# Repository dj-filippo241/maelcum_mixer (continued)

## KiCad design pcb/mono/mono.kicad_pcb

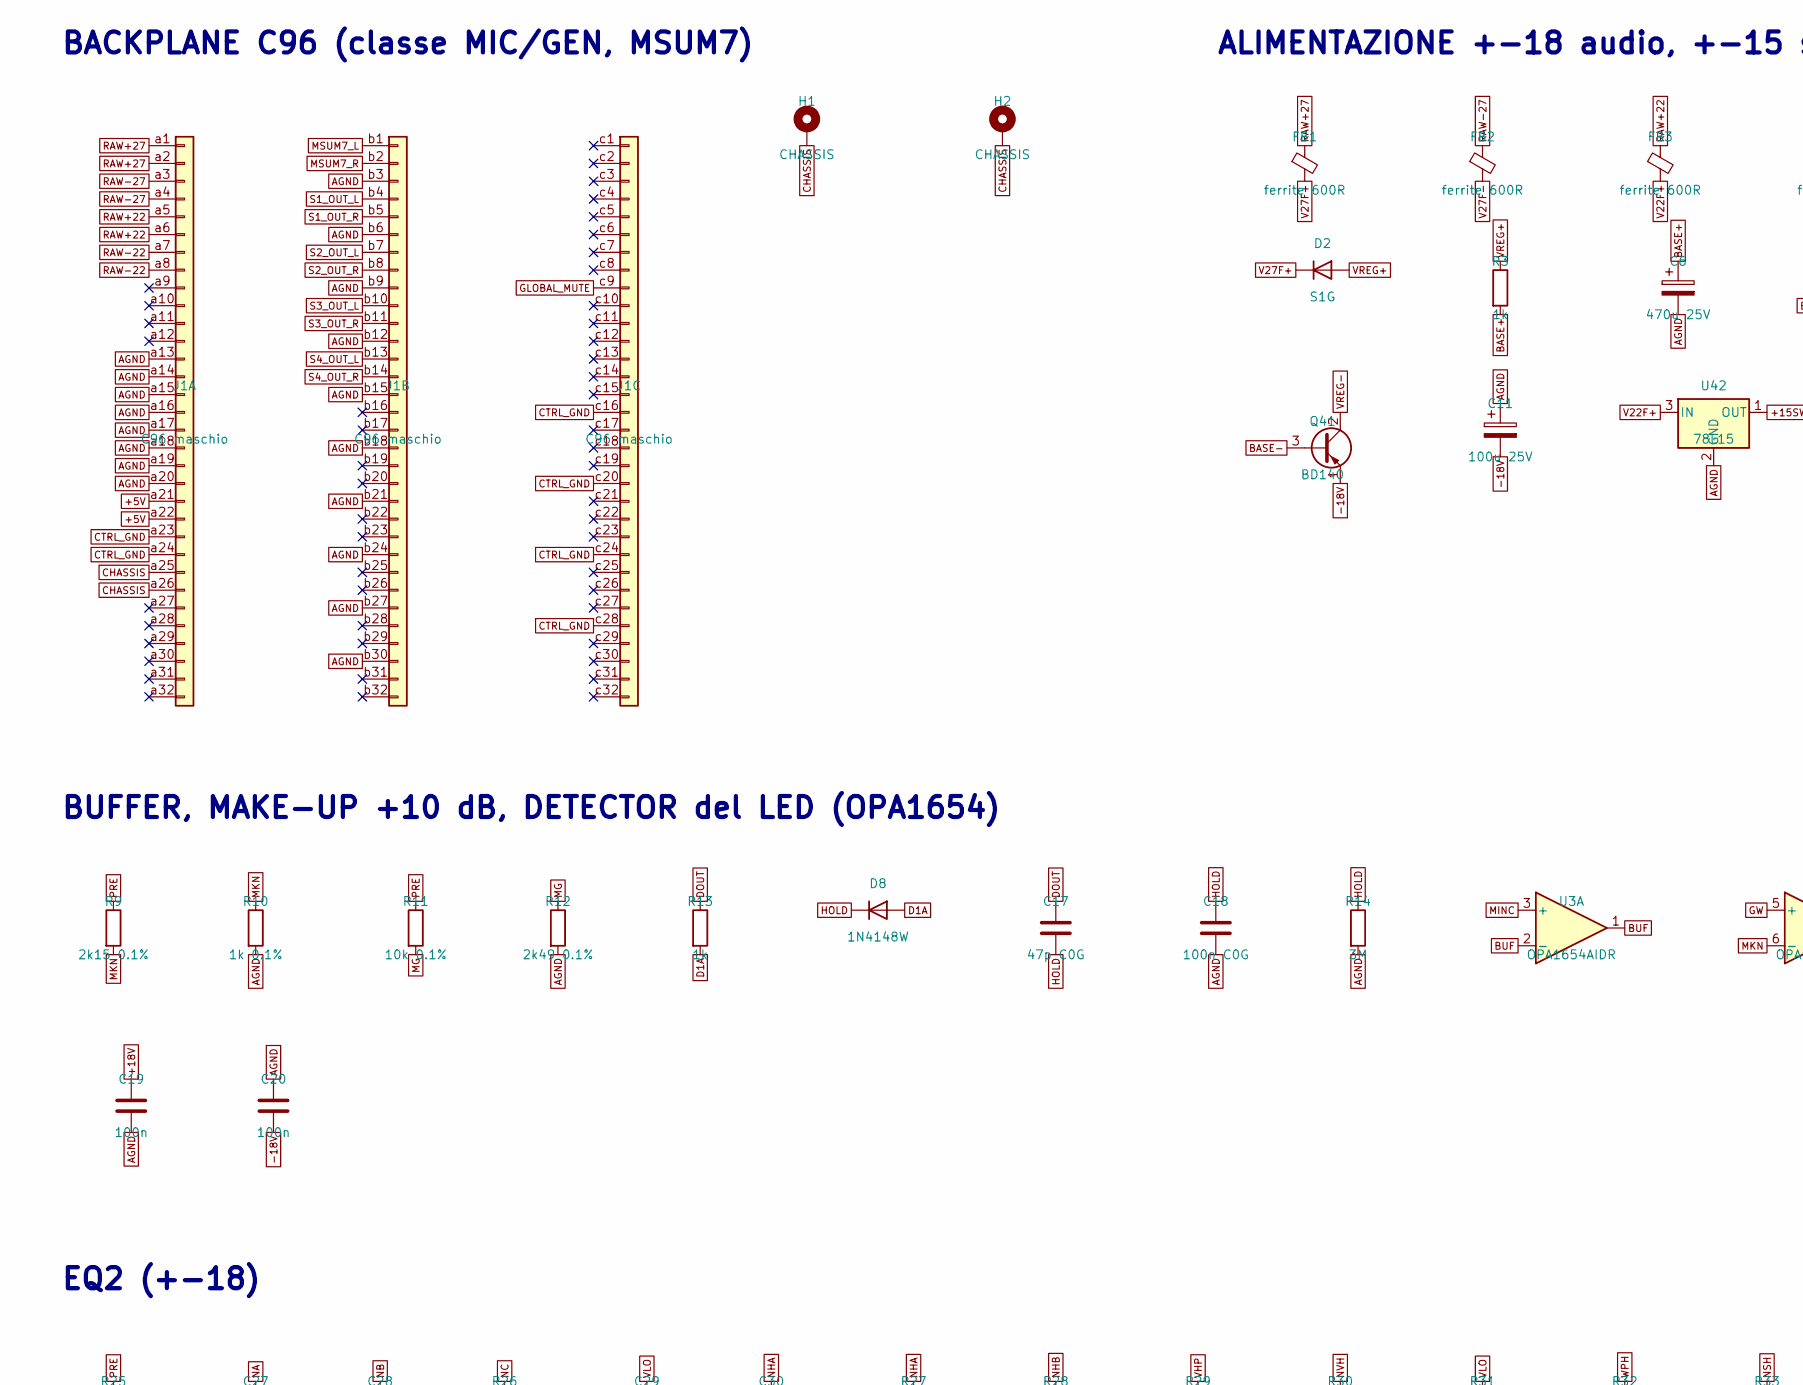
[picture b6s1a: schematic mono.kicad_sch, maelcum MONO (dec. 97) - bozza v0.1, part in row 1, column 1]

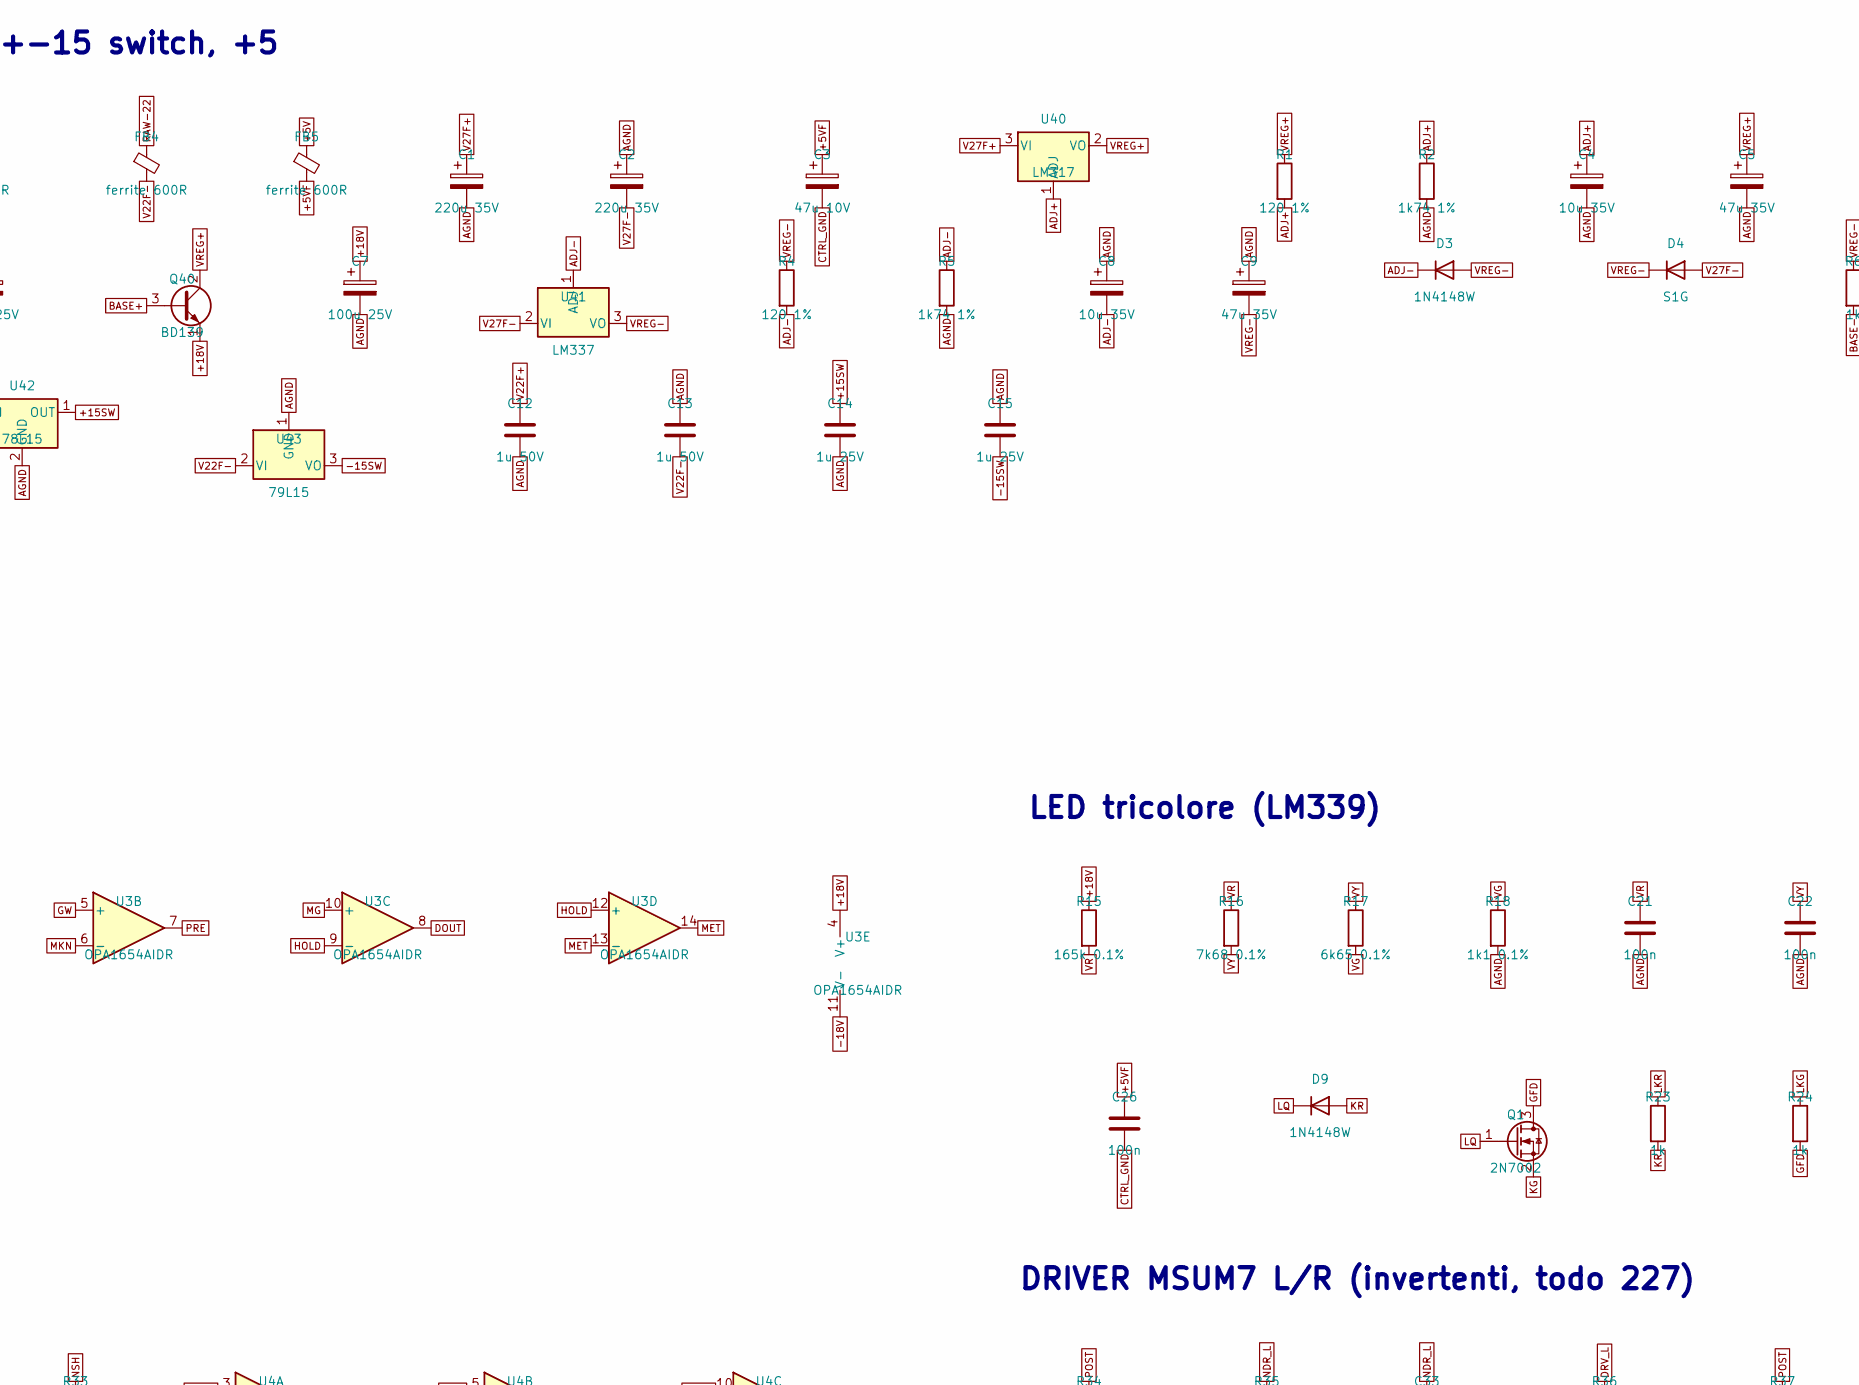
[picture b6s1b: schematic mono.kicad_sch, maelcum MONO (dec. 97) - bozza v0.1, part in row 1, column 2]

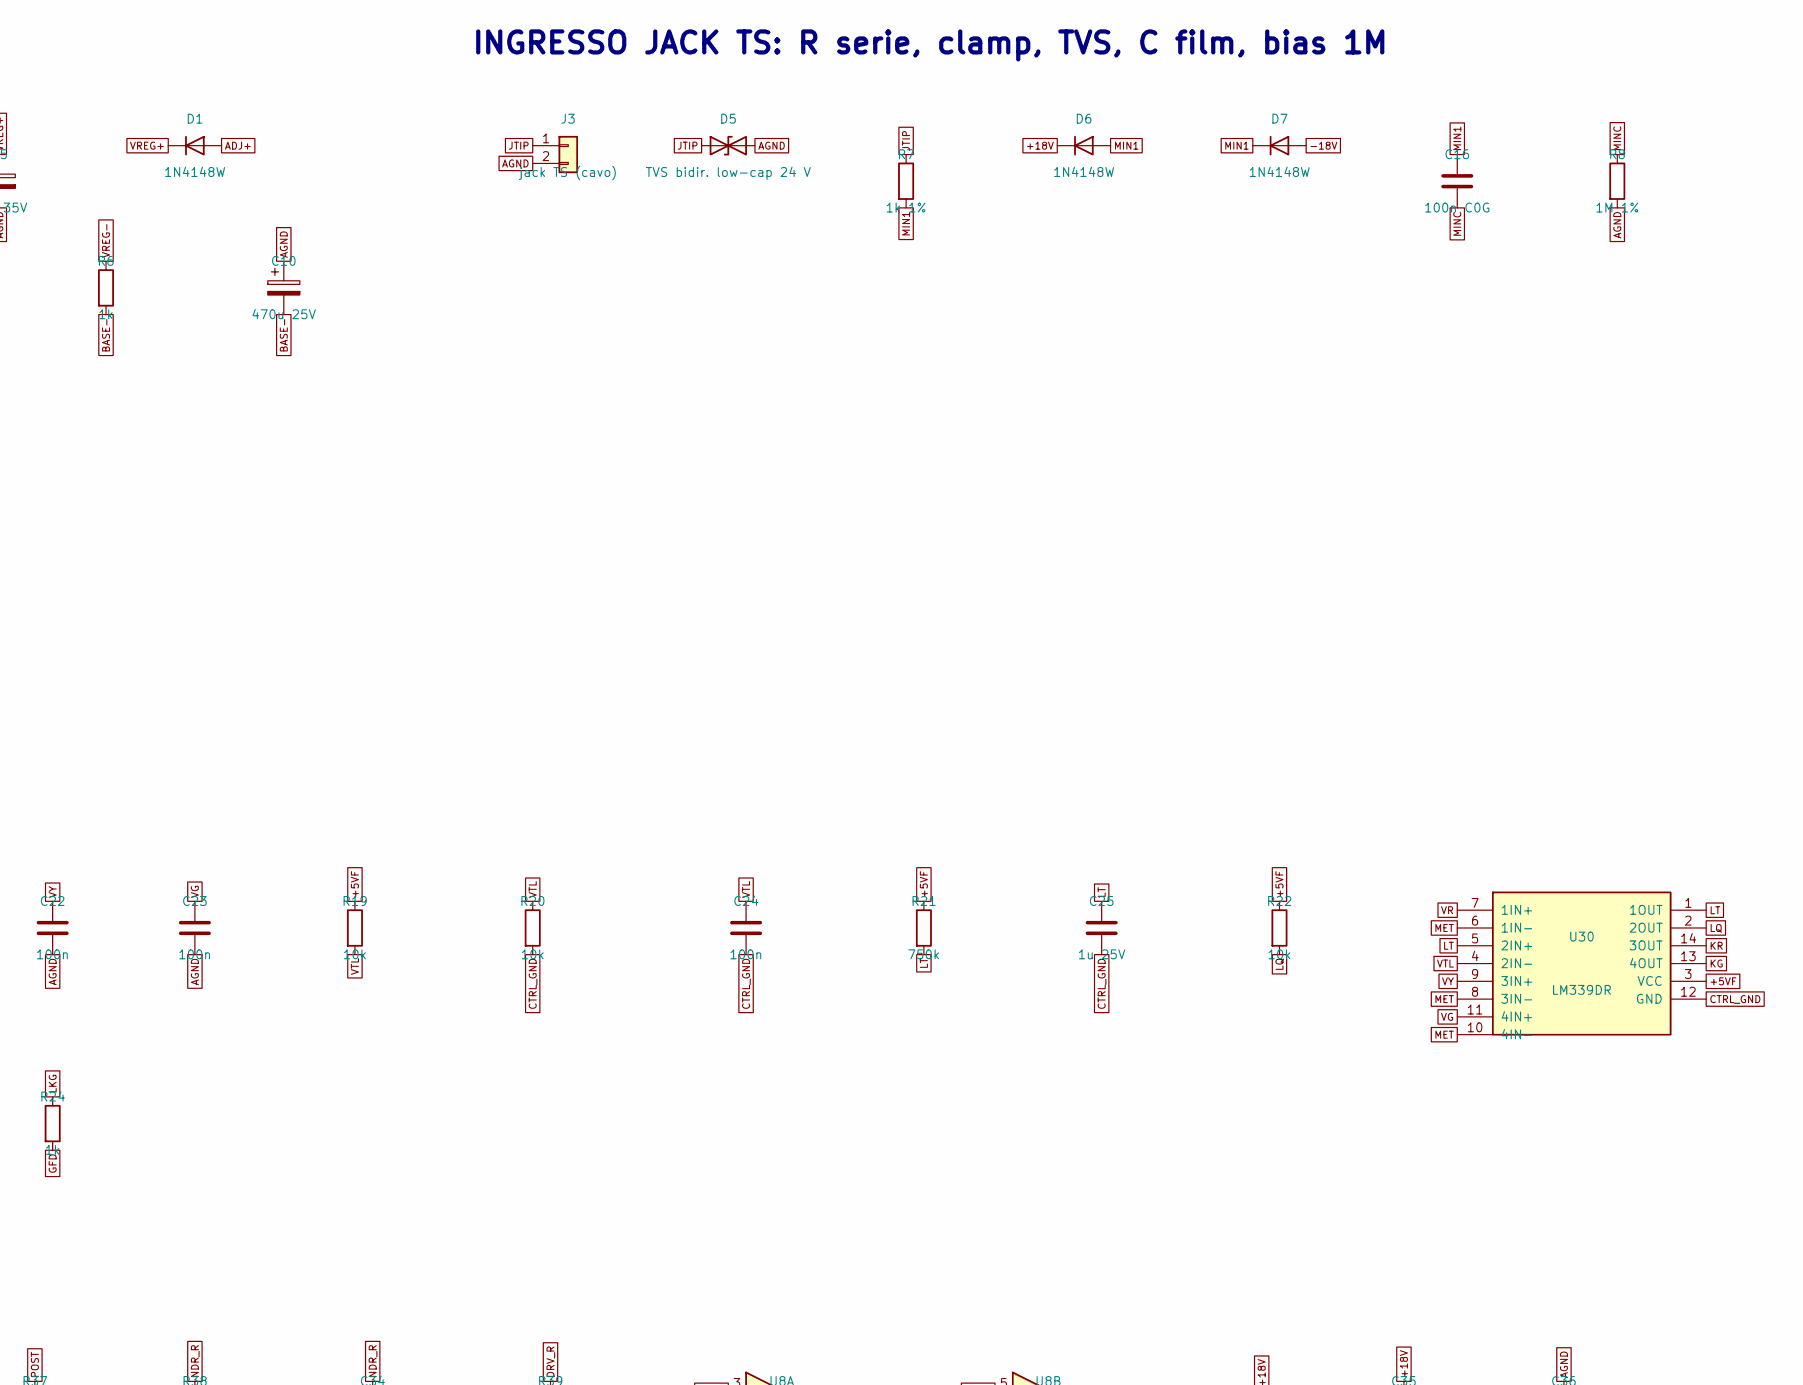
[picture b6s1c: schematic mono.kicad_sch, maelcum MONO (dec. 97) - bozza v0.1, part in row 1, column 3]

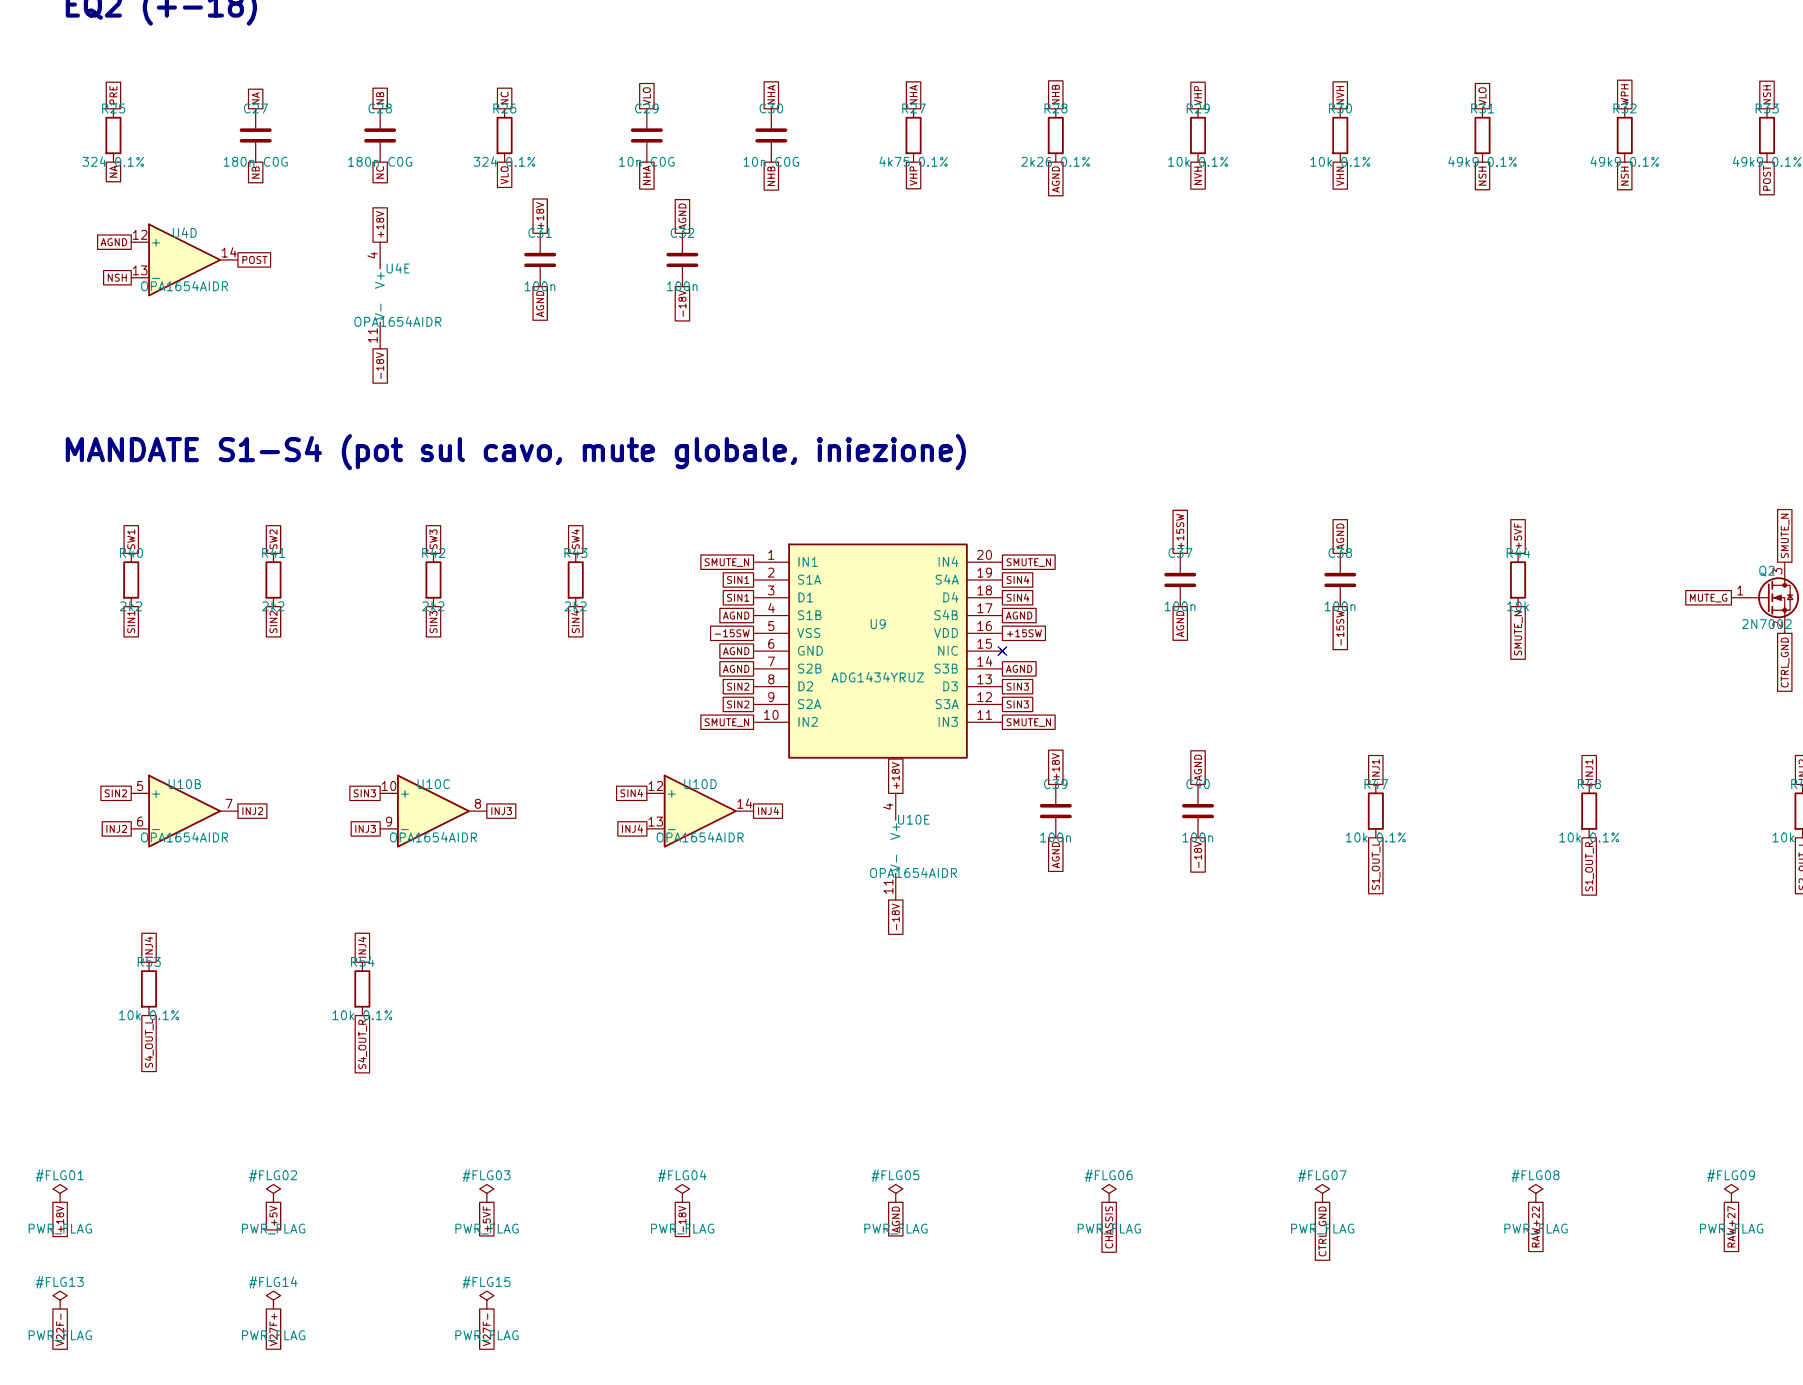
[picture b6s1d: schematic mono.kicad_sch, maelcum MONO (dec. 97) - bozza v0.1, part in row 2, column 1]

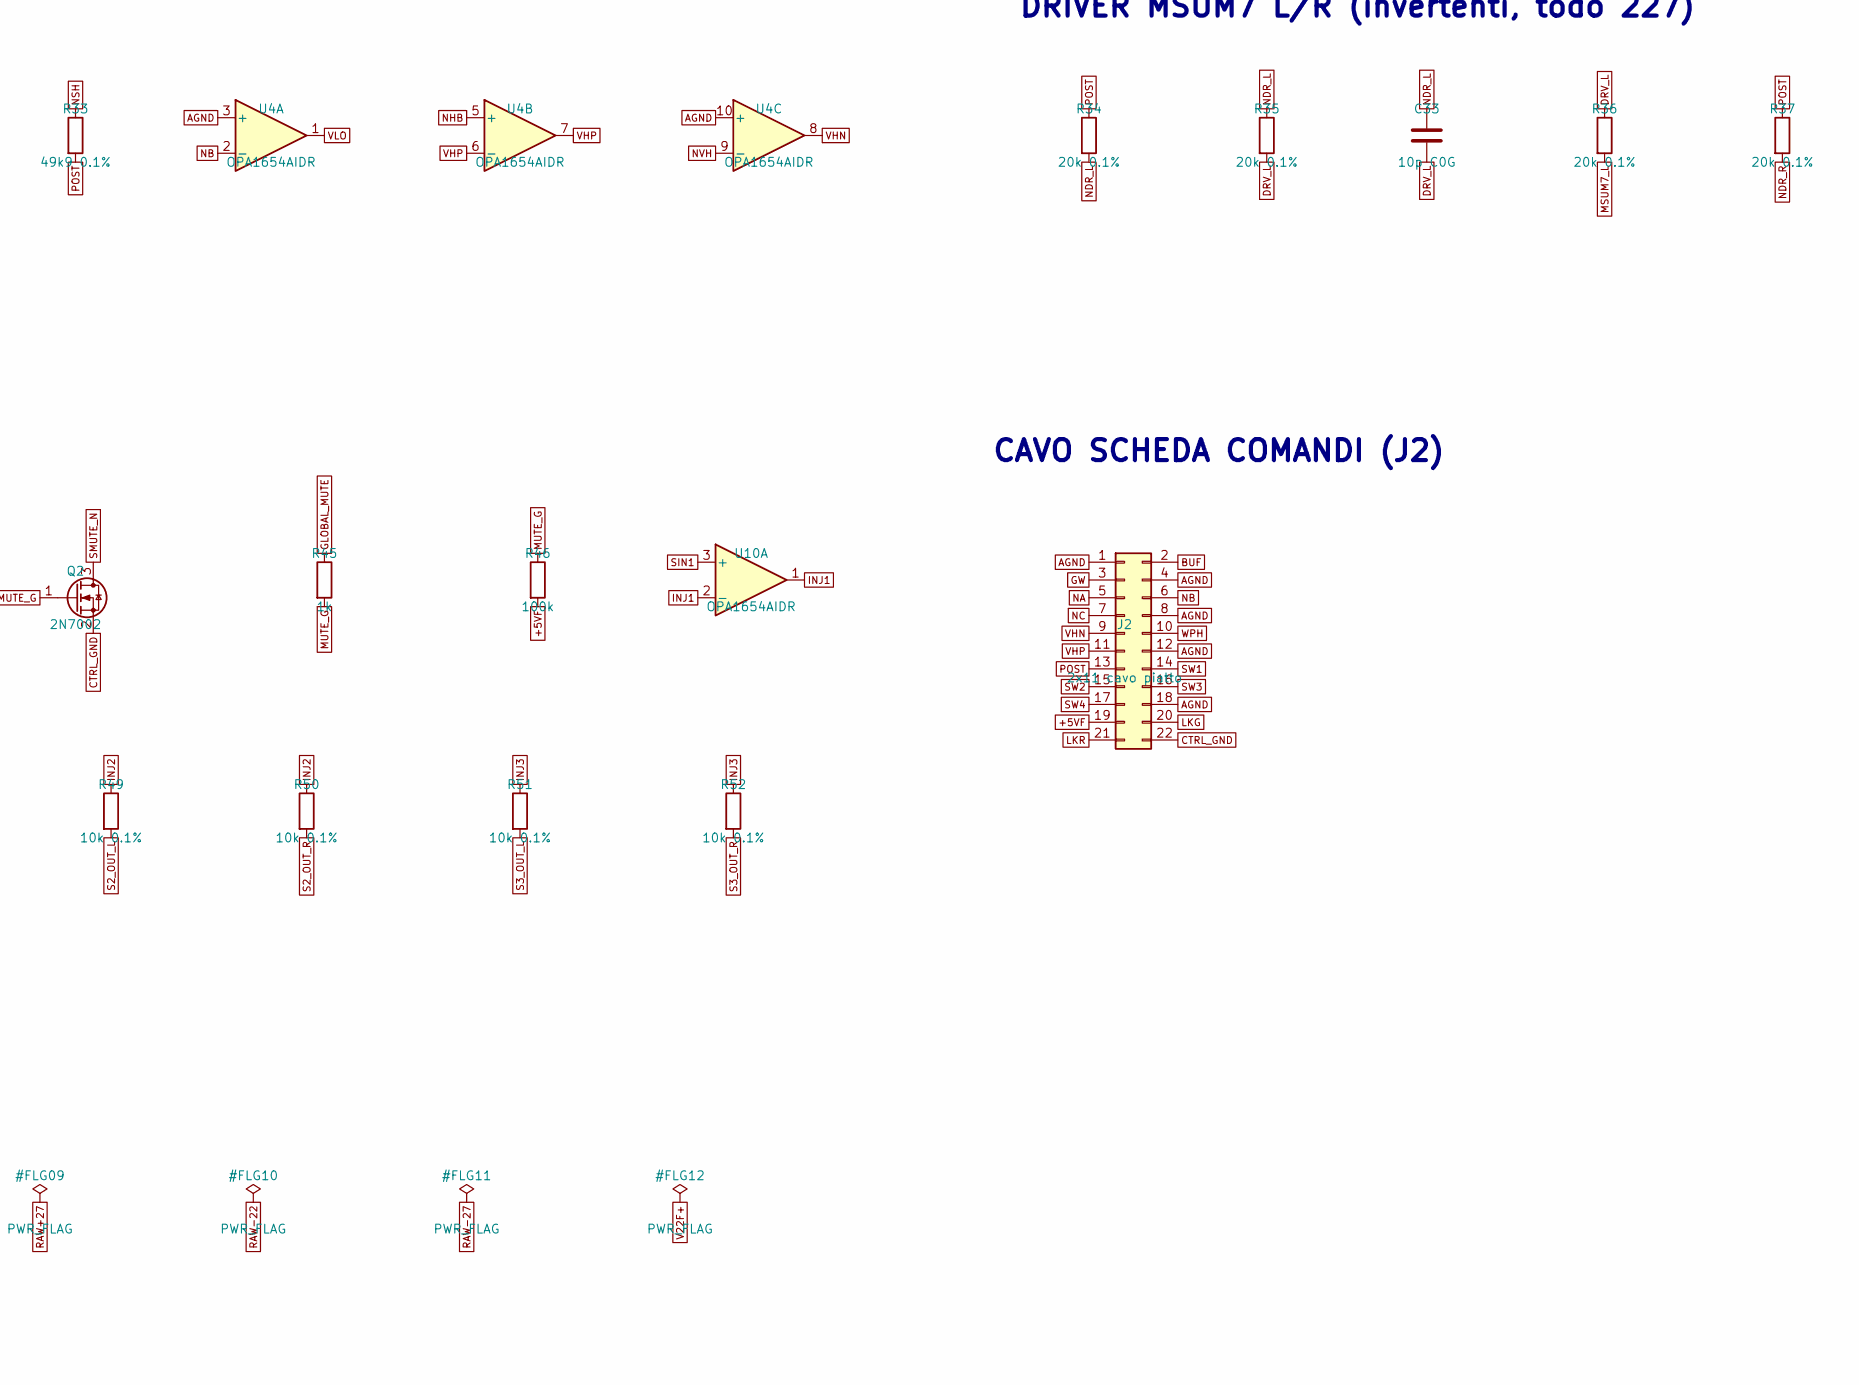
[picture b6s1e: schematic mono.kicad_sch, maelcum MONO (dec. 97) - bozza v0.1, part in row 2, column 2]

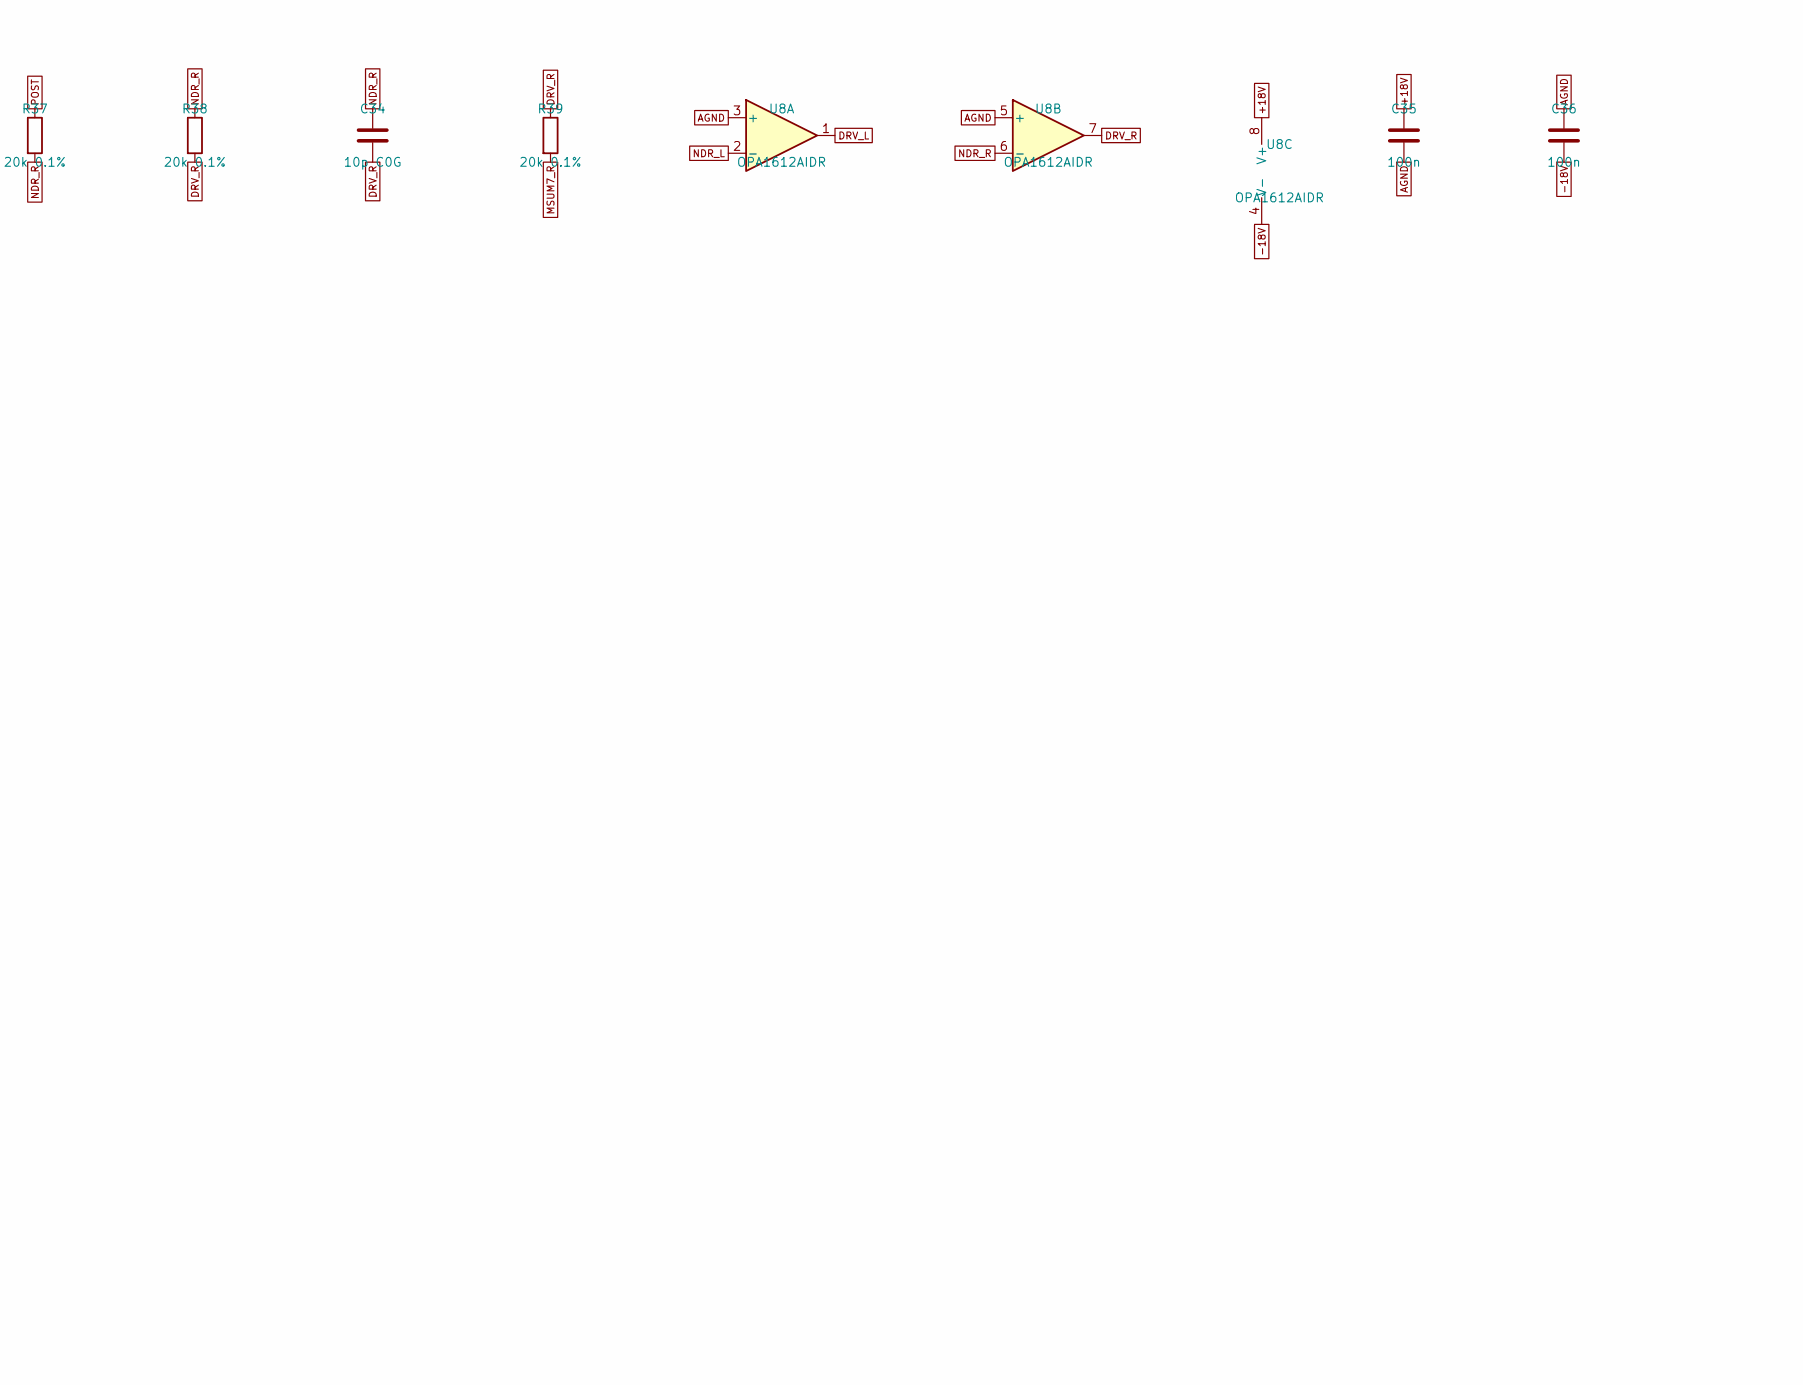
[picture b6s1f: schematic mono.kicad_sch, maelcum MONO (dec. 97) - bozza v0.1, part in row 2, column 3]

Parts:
C1, C2: 220u 35V; CP_Radial_D8.0mm_P3.50mm
C3: 47u 10V; CP_Radial_D5.0mm_P2.00mm
C4, C8: 10u 35V; CP_Radial_D5.0mm_P2.00mm
C5, C9: 47u 35V; CP_Radial_D6.3mm_P2.50mm
C6, C10: 470u 25V; CP_Radial_D8.0mm_P3.50mm
C7, C11: 100u 25V; CP_Radial_D6.3mm_P2.50mm
C12, C13: 1u 50V; C_1206_3216Metric
C14, C15, C25: 1u 25V; C_1206_3216Metric
C16, C18: 100n C0G; C_1206_3216Metric
C17: 47p C0G; C_0805_2012Metric
C19, C20, C21, C22, C23, C24, C26, C31, C32, C35, C36, C37, C38, C39, C40: 100n; C_0805_2012Metric
C27, C28: 180n C0G; C_1206_3216Metric
C29, C30: 10n C0G; C_1206_3216Metric
C33, C34: 10p C0G; C_0805_2012Metric
D1, D3, D6, D7, D8, D9: 1N4148W; D_SOD-123
D2, D4: S1G; D_SMA
D5: TVS bidir. low-cap 24 V; D_SOD-323
FB1, FB2, FB3, FB4, FB5: ferrite 600R; L_1206_3216Metric
H1, H2: CHASSIS; MountingHole_3.2mm_M3_Pad
J1: C96 maschio; DIN41612_C_3x32_Male_Horizontal_THT
J2: 2x11 cavo piatto; PinHeader_2x11_P2.54mm_Vertical
J3: jack TS (cavo); PinHeader_1x02_P2.54mm_Vertical
Q1, Q2: 2N7002; SOT-23
Q40: BD139; TO-126-3_Vertical
Q41: BD140; TO-126-3_Vertical
R1, R4: 120 1%; R_0805_2012Metric
R2, R5: 1k74 1%; R_0805_2012Metric
R3, R6, R13, R23, R24, R45: 1k; R_0805_2012Metric
R7: 1k 1%; R_0805_2012Metric
R8: 1M 1%; R_0805_2012Metric
R9: 2k15 0.1%; R_0805_2012Metric
R10: 1k 0.1%; R_0805_2012Metric
R11, R29, R30, R47, R48, R49, R50, R51, R52, R53, R54: 10k 0.1%; R_0805_2012Metric
R12: 2k49 0.1%; R_0805_2012Metric
R14: 3M; R_0805_2012Metric
R15: 165k 0.1%; R_0805_2012Metric
R16: 7k68 0.1%; R_0805_2012Metric
R17: 6k65 0.1%; R_0805_2012Metric
R18: 1k1 0.1%; R_0805_2012Metric
R19, R20, R22, R44: 10k; R_0805_2012Metric
R21: 750k; R_0805_2012Metric
R25, R26: 324 0.1%; R_0805_2012Metric
R27: 4k75 0.1%; R_0805_2012Metric
R28: 2k26 0.1%; R_0805_2012Metric
R31, R32, R33: 49k9 0.1%; R_0805_2012Metric
R34, R35, R36, R37, R38, R39: 20k 0.1%; R_0805_2012Metric
R40, R41, R42, R43: 2k2; R_0805_2012Metric
R46: 100k; R_0805_2012Metric
U3, U4, U10: OPA1654AIDR; SOIC-14_3.9x8.7mm_P1.27mm
U8: OPA1612AIDR; SOIC-8_3.9x4.9mm_P1.27mm
U9: ADG1434YRUZ; TSSOP-20_4.4x6.5mm_P0.65mm
U30: LM339DR; SOIC-14_3.9x8.7mm_P1.27mm
U40: LM317; TO-220-3_Vertical
U41: LM337; TO-220-3_Vertical
U42: 78L15; SOT-89-3
U43: 79L15; SOT-89-3

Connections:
+5V: FB5.1, J1.a21, J1.a22
+5VF: C3.1, C26.1, FB5.2, J2.19, R19.1, R21.1, R22.1, R44.1, R46.2, U30.3 (VCC)
+15SW: C14.1, C37.1, U9.16 (VDD), U42.1 (OUT)
+18V: C7.1, C19.1, C31.1, C35.1, C39.1, D6.1 (K), Q40.1 (E), R15.1, U3.4 (V+), U4.4 (V+), U8.8 (V+), U10.4 (V+)
-15SW: C15.2, C38.2, U9.5 (VSS), U43.3 (VO)
-18V: C11.2, C20.2, C32.2, C36.2, C40.2, D7.2 (A), Q41.1 (E), U3.11 (V-), U4.11 (V-), U8.4 (V-), U10.11 (V-)
ADJ+: C4.1, D1.2 (A), R1.2, R2.1, U40.1 (ADJ)
ADJ-: C8.2, D3.1 (K), R4.2, R5.1, U41.1 (ADJ)
AGND: C1.2, C2.1, C4.2, C5.2, C6.2, C7.2, C8.1, C9.1, C10.1, C11.1, C12.2, C13.1, C14.2, C15.1, C18.2, C19.2, C20.1, C21.2, C22.2, C23.2, C31.2, C32.1, C35.2, C36.1, C37.2, C38.1, C39.2, C40.1, D5.2 (A2), J1.a13, J1.a14, J1.a15, J1.a16, J1.a17, J1.a18, J1.a19, J1.a20, J1.b3, J1.b6, J1.b9, J1.b12, J1.b15, J1.b18, J1.b21, J1.b24, J1.b27, J1.b30, J2.1, J2.4, J2.8, J2.12, J2.18, J3.2, R2.2, R5.2, R8.2, R10.2, R12.2, R14.2, R18.2, R28.2, U4.3 (+), U4.10 (+), U4.12 (+), U8.3 (+), U8.5 (+), U9.4 (S1B), U9.6 (GND), U9.7 (S2B), U9.14 (S3B), U9.17 (S4B), U42.2 (GND), U43.1 (GND)
BASE+: C6.1, Q40.3 (B), R3.2
BASE-: C10.2, Q41.3 (B), R6.2
BUF: J2.2, U3.1, U3.2 (-)
CHASSIS: H1.1, H2.1, J1.a25, J1.a26
CTRL_GND: C3.2, C24.2, C25.2, C26.2, J1.a23, J1.a24, J1.c16, J1.c20, J1.c24, J1.c28, J2.22, Q2.2 (S), R20.2, U30.12 (GND)
D1A: D8.2 (A), R13.2
DOUT: C17.1, R13.1, U3.8
DRV_L: C33.2, R35.2, R36.1, U8.1
DRV_R: C34.2, R38.2, R39.1, U8.7
GFD: Q1.3 (D), R24.2
GLOBAL_MUTE: J1.c9, R45.1
GW: J2.3, U3.5 (+)
HOLD: C17.2, C18.1, D8.1 (K), R14.1, U3.9 (-), U3.12 (+)
INJ1: R47.1, R48.1, U10.1, U10.2 (-)
INJ2: R49.1, R50.1, U10.6 (-), U10.7
INJ3: R51.1, R52.1, U10.8, U10.9 (-)
INJ4: R53.1, R54.1, U10.13 (-), U10.14
JTIP: D5.1 (A1), J3.1, R7.1
KG: Q1.2 (S), U30.13 (4OUT)
KR: D9.2 (A), R23.2, U30.14 (3OUT)
LKG: J2.20, R24.1
LKR: J2.21, R23.1
LQ: D9.1 (K), Q1.1 (G), R22.2, U30.2 (2OUT)
LT: C25.1, R21.2, U30.1 (1OUT), U30.5 (2IN+)
MET: U3.13 (-), U3.14, U30.6 (1IN-), U30.8 (3IN-), U30.10 (4IN-)
MG: R11.2, R12.1, U3.10 (+)
MIN1: C16.1, D6.2 (A), D7.1 (K), R7.2
MINC: C16.2, R8.1, U3.3 (+)
MKN: R9.2, R10.1, U3.6 (-)
MSUM7_L: J1.b1, R36.2
MSUM7_R: J1.b2, R39.2
MUTE_G: Q2.1 (G), R45.2, R46.1
NA: C27.1, J2.5, R25.2
NB: C27.2, C28.1, J2.6, U4.2 (-)
NC: C28.2, J2.7, R26.1
NDR_L: C33.1, R34.2, R35.1, U8.2 (-)
NDR_R: C34.1, R37.2, R38.1, U8.6 (-)
NHA: C29.2, C30.1, R27.1
NHB: C30.2, R28.1, U4.5 (+)
NSH: R31.2, R32.2, R33.1, U4.13 (-)
NVH: R29.2, R30.1, U4.9 (-)
POST: J2.13, R33.2, R34.1, R37.1, U4.14
PRE: R9.1, R11.1, R25.1, U3.7
RAW+22: FB3.1, J1.a5, J1.a6
RAW+27: FB1.1, J1.a1, J1.a2
RAW-22: FB4.1, J1.a7, J1.a8
RAW-27: FB2.1, J1.a3, J1.a4
S1_OUT_L: J1.b4, R47.2
S1_OUT_R: J1.b5, R48.2
S2_OUT_L: J1.b7, R49.2
S2_OUT_R: J1.b8, R50.2
S3_OUT_L: J1.b10, R51.2
S3_OUT_R: J1.b11, R52.2
S4_OUT_L: J1.b13, R53.2
S4_OUT_R: J1.b14, R54.2
SIN1: R40.2, U9.2 (S1A), U9.3 (D1), U10.3 (+)
SIN2: R41.2, U9.8 (D2), U9.9 (S2A), U10.5 (+)
SIN3: R42.2, U9.12 (S3A), U9.13 (D3), U10.10 (+)
SIN4: R43.2, U9.18 (D4), U9.19 (S4A), U10.12 (+)
SMUTE_N: Q2.3 (D), R44.2, U9.1 (IN1), U9.10 (IN2), U9.11 (IN3), U9.20 (IN4)
SW1: J2.14, R40.1
SW2: J2.15, R41.1
SW3: J2.16, R42.1
SW4: J2.17, R43.1
V22F+: C12.1, FB3.2, U42.3 (IN)
V22F-: C13.2, FB4.2, U43.2 (VI)
V27F+: C1.1, D2.1 (K), FB1.2, U40.3 (VI)
V27F-: C2.2, D4.2 (A), FB2.2, U41.2 (VI)
VG: C23.1, R17.2, R18.1, U30.11 (4IN+)
VHN: J2.9, R30.2, U4.8
VHP: J2.11, R27.2, R29.1, U4.6 (-), U4.7
VLO: C29.1, R26.2, R31.1, U4.1
VR: C21.1, R15.2, R16.1, U30.7 (1IN+)
VREG+: C5.1, D1.1 (K), D2.2 (A), Q40.2 (C), R1.1, R3.1, U40.2 (VO)
VREG-: C9.2, D3.2 (A), D4.1 (K), Q41.2 (C), R4.1, R6.1, U41.3 (VO)
VTL: C24.1, R19.2, R20.1, U30.4 (2IN-)
VY: C22.1, R16.2, R17.1, U30.9 (3IN+)
WPH: J2.10, R32.1

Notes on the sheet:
BACKPLANE C96 (classe MIC/GEN, MSUM7)
ALIMENTAZIONE +-18 audio, +-15 switch, +5
INGRESSO JACK TS: R serie, clamp, TVS, C film, bias 1M
BUFFER, MAKE-UP +10 dB, DETECTOR del LED (OPA1654)
LED tricolore (LM339)
EQ2 (+-18)
DRIVER MSUM7 L/R (invertenti, todo 227)
MANDATE S1-S4 (pot sul cavo, mute globale, iniezione)
CAVO SCHEDA COMANDI (J2)

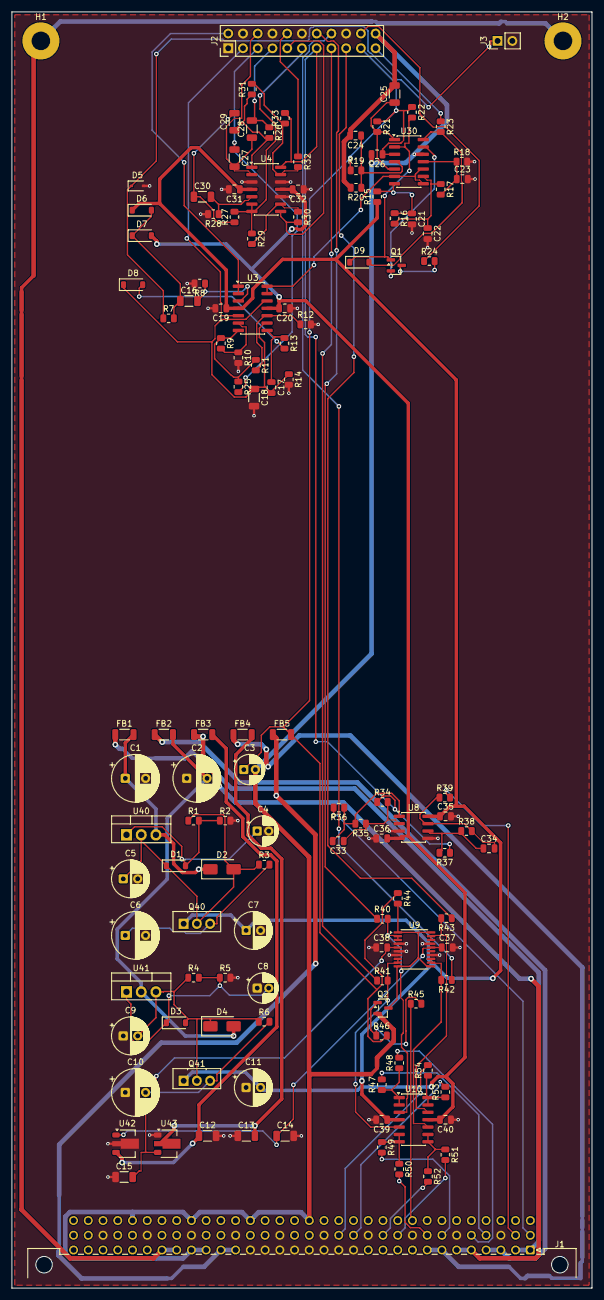
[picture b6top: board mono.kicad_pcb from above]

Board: 4 copper layers, 100.0 x 220.0 mm, 127 parts (0 on the bottom side), 87 nets.

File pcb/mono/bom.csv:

quantita;valore;impronta;riferimenti;nota
2;220u 35V;CP_Radial_D8.0mm_P3.50mm;C1 C2;
2;1u 50V;C_1206_3216Metric;C12 C13;
3;1u 25V;C_1206_3216Metric;C14 C15 C25;
1;100n C0G;C_1206_3216Metric;C16;film o C0G: polo 1,6 Hz col bias 1M
1;47p C0G;C_0805_2012Metric;C17;
1;100n C0G;C_1206_3216Metric;C18;hold: niente altro sul nodo (sim/meter)
15;100n;C_0805_2012Metric;C19 C20 C21 C22 C23 C24 C26 C31 C32 C35 C36 C37 C38 C39 C40;
2;180n C0G;C_1206_3216Metric;C27 C28;
2;10n C0G;C_1206_3216Metric;C29 C30;
1;47u 10V;CP_Radial_D5.0mm_P2.00mm;C3;
2;10p C0G;C_0805_2012Metric;C33 C34;NOTA: Cf come i ricevitori a massa virtuale
2;10u 35V;CP_Radial_D5.0mm_P2.00mm;C4 C8;
2;47u 35V;CP_Radial_D6.3mm_P2.50mm;C5 C9;
2;470u 25V;CP_Radial_D8.0mm_P3.50mm;C6 C10;
2;100u 25V;CP_Radial_D6.3mm_P2.50mm;C7 C11;
1;1N4148W;D_SOD-123;D1;scarica Cadj
1;S1G;D_SMA;D2;protezione inversa
3;1N4148W;D_SOD-123;D3 D7 D8;
1;S1G;D_SMA;D4;
1;TVS bidir. low-cap 24 V;D_SOD-323;D5;NOTA: tensione di lavoro sopra gli 8,7 Vp di +18 dBu
1;1N4148W;D_SOD-123;D6;NOTA: clamp 1N4148W al posto del BAV199 (pinout non verificato)
1;1N4148W;D_SOD-123;D9;rosso acceso durante il latch
5;ferrite 600R;L_1206_3216Metric;FB1 FB2 FB3 FB4 FB5;
1;C96 maschio;DIN41612_C_3x32_Male_Horizontal_THT;J1;DIN 41612 C 3x32, angolo retto
1;2x11 cavo piatto;PinHeader_2x11_P2.54mm_Vertical;J2;cavo piatto corto (<= 10 cm) verso la scheda comandi dietro il pannello (dec. 133)
1;jack TS (cavo);PinHeader_1x02_P2.54mm_Vertical;J3;NOTA: cavo verso il jack TS; sleeve ad AGND del modulo (grounding §4)
1;2N7002;SOT-23;Q1;spegne il verde durante il latch del rosso
1;2N7002;SOT-23;Q2;GLOBAL_MUTE alto = muto
1;BD139;TO-126-3_Vertical;Q40;
1;BD140;TO-126-3_Vertical;Q41;
2;120 1%;R_0805_2012Metric;R1 R4;
1;1k 0.1%;R_0805_2012Metric;R10;G = 3,15 = +9,97 dB
11;10k 0.1%;R_0805_2012Metric;R11 R29 R30 R47 R48 R49 R50 R51 R52 R53 R54;
1;2k49 0.1%;R_0805_2012Metric;R12;
1;3M;R_0805_2012Metric;R14;release 0,3 s (dec. 81)
1;165k 0.1%;R_0805_2012Metric;R15;
1;7k68 0.1%;R_0805_2012Metric;R16;
1;6k65 0.1%;R_0805_2012Metric;R17;
1;1k1 0.1%;R_0805_2012Metric;R18;
3;10k;R_0805_2012Metric;R19 R20 R22;
1;1k74 1%;R_0805_2012Metric;R2;E96 1,74k = 19,4 V (fx-send NOTE punto 16)
1;750k;R_0805_2012Metric;R21;latch del rosso: 0,69 x 750k x 1u = 0,52 s
1;1k;R_0805_2012Metric;R23;~2,8 mA nel rosso (LED alta efficienza, metering §1)
1;1k;R_0805_2012Metric;R24;~2,8 mA nel verde
2;324 0.1%;R_0805_2012Metric;R25 R26;
1;4k75 0.1%;R_0805_2012Metric;R27;NOTA: mic-mono §5.1 dice 4,7k/2,25k (~5 kHz); backend.inc 5,23k/2,5k
1;2k26 0.1%;R_0805_2012Metric;R28;E96 di 2,25k
1;1k;R_0805_2012Metric;R3;NOTA: cap-moltiplicatore come il FX-SEND (~50 mA)
3;49k9 0.1%;R_0805_2012Metric;R31 R32 R33;
4;20k 0.1%;R_0805_2012Metric;R34 R35 R37 R38;
2;20k 0.1%;R_0805_2012Metric;R36 R39;R di somma lato sorgente (dec. 97)
4;2k2;R_0805_2012Metric;R40 R41 R42 R43;
1;10k;R_0805_2012Metric;R44;IN alto = suona (VIH 2,0 V)
1;100k;R_0805_2012Metric;R46;senza master il modulo resta muto (fail-safe, fx-send NOTE 5)
1;1k74 1%;R_0805_2012Metric;R5;
3;1k;R_0805_2012Metric;R6 R13 R45;
1;1k 1%;R_0805_2012Metric;R7;
1;1M 1%;R_0805_2012Metric;R8;Zin 1 MOhm
1;2k15 0.1%;R_0805_2012Metric;R9;
1;OPA1654AIDR;SOIC-14_3.9x8.7mm_P1.27mm;U10;buffer d'iniezione, non invertenti
1;OPA1654AIDR;SOIC-14_3.9x8.7mm_P1.27mm;U3;buffer 1 MOhm, make-up (pot GAIN 10k A sul cavo: AGND-GW-BUF), superdiodo e buffer del LED
1;LM339DR;SOIC-14_3.9x8.7mm_P1.27mm;U30;NOTA: GND a CTRL_GND (correnti dei LED fuori da AGND); ingressi riferiti ad AGND
1;OPA1654AIDR;SOIC-14_3.9x8.7mm_P1.27mm;U4;EQ2: LOW, HIGH follower, HIGH invertente, HIGH somma
1;LM317;TO-220-3_Vertical;U40;
1;LM337;TO-220-3_Vertical;U41;
1;78L15;SOT-89-3;U42;
1;79L15;SOT-89-3;U43;
1;OPA1612AIDR;SOIC-8_3.9x4.9mm_P1.27mm;U8;driver MSUM invertenti (F2)
1;ADG1434YRUZ;TSSOP-20_4.4x6.5mm_P0.65mm;U9;mute globale delle mandate (dec. 94b): D e SxA sul nodo, SxB a massa
